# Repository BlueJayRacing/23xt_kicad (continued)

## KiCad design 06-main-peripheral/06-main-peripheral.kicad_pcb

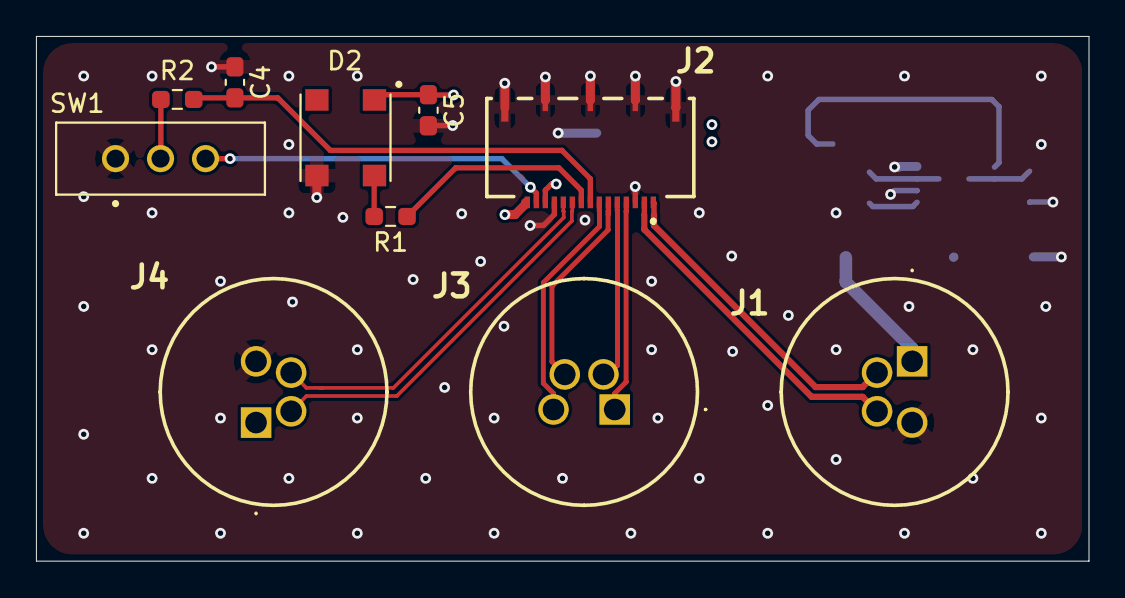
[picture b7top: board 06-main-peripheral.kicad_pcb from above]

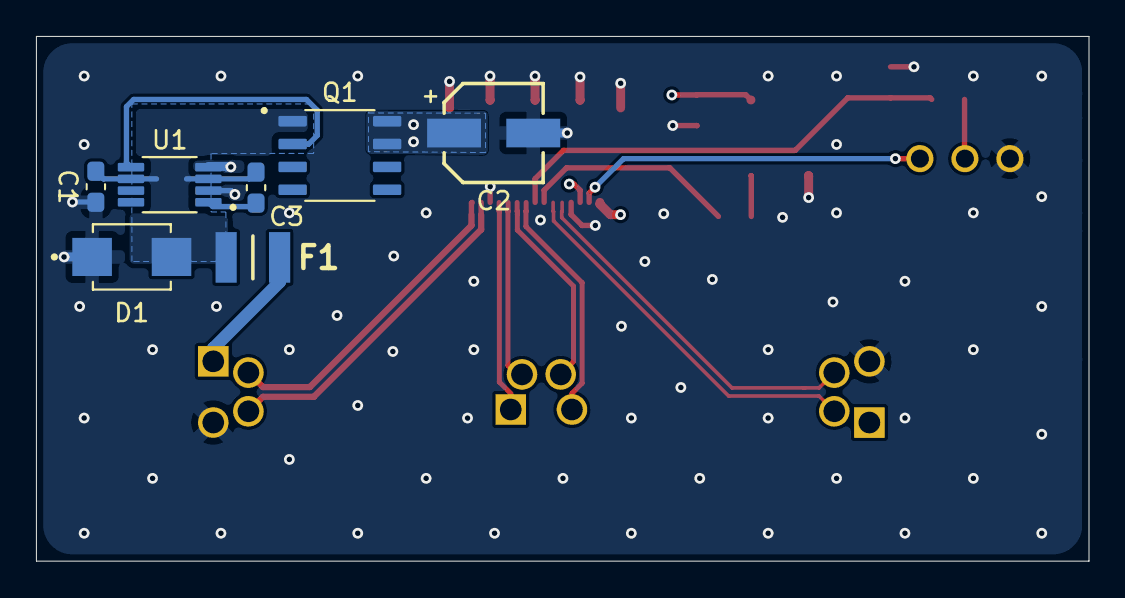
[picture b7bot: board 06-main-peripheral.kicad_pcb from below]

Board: 4 copper layers, 58.5 x 29.2 mm, 17 parts (7 on the bottom side), 20 nets.

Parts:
C1: 22nF; C_0603_1608Metric_Pad1.08x0.95mm_HandSolder
C2: 47uF; WCAP-ASLI_5X5.5_DXL_
C3: 0.1uF; C_0603_1608Metric_Pad1.08x0.95mm_HandSolder
C4, C5: 100nF; C_0603_1608Metric_Pad1.08x0.95mm_HandSolder
D1: SMBJ6.0CA; DIOM4336X265N
D2: LED 5050
F1: 0ZCH0050FF2G
J1, J3, J4: T4040014041000
J2: FH-41-15S-0.5SH-05_; FH4115S05SH05
Q1: DMN3018SSD-13; SOIC127P600X170-8N
R1: 500; R_0603_1608Metric_Pad0.98x0.95mm_HandSolder
R2: 10k; R_0603_1608Metric_Pad0.98x0.95mm_HandSolder
SW1: 100SP1K1B25M1QEH-ND; SW_EG1218
U1: LM74700-Q1; LM74610QDGKRQ1

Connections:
3.3V: J2.14, SW1.3 (A)
5V: C5.1, D2.3 (VDD), J2.15, J4.1
CAN_N: J2.11, J4.4
CAN_P: J2.10, J4.2
GND: C1.2, C2.2, C4.1, C5.2, D1.1 (A1), D2.1 (GND), J1.3, J2.3, J2.12, J2.G1, J2.G2, J2.G3, J2.MP2, J4.3, SW1.1 (C), U1.2 (GND), U1.4 (CATHODE)
LED_CONTROL: J2.9, R1.1
unnamed: C1.1, C3.1, D1.2 (A2), F1.1, Q1.1 (S), U1.3 (EN), U1.6 (ANODE)
unnamed: D2.2 (DIN), R1.2
unnamed: F1.2, J1.1
unnamed: Q1.2 (G), U1.5 (GATE)
unnamed: R2.2, SW1.2 (B)
unnamed: C3.2, U1.1 (VCAP)
RX_N: J2.5, J3.2
RX_P: J2.4, J3.1
TX_N: J2.6, J3.4
TX_P: J2.7, J3.3
USB_5V: C2.1, J2.13, Q1.7 (D), Q1.8
USB_D_N: J1.2, J2.1
USB_D_P: J1.4, J2.2
USB_SEL: C4.2, J2.8, R2.1

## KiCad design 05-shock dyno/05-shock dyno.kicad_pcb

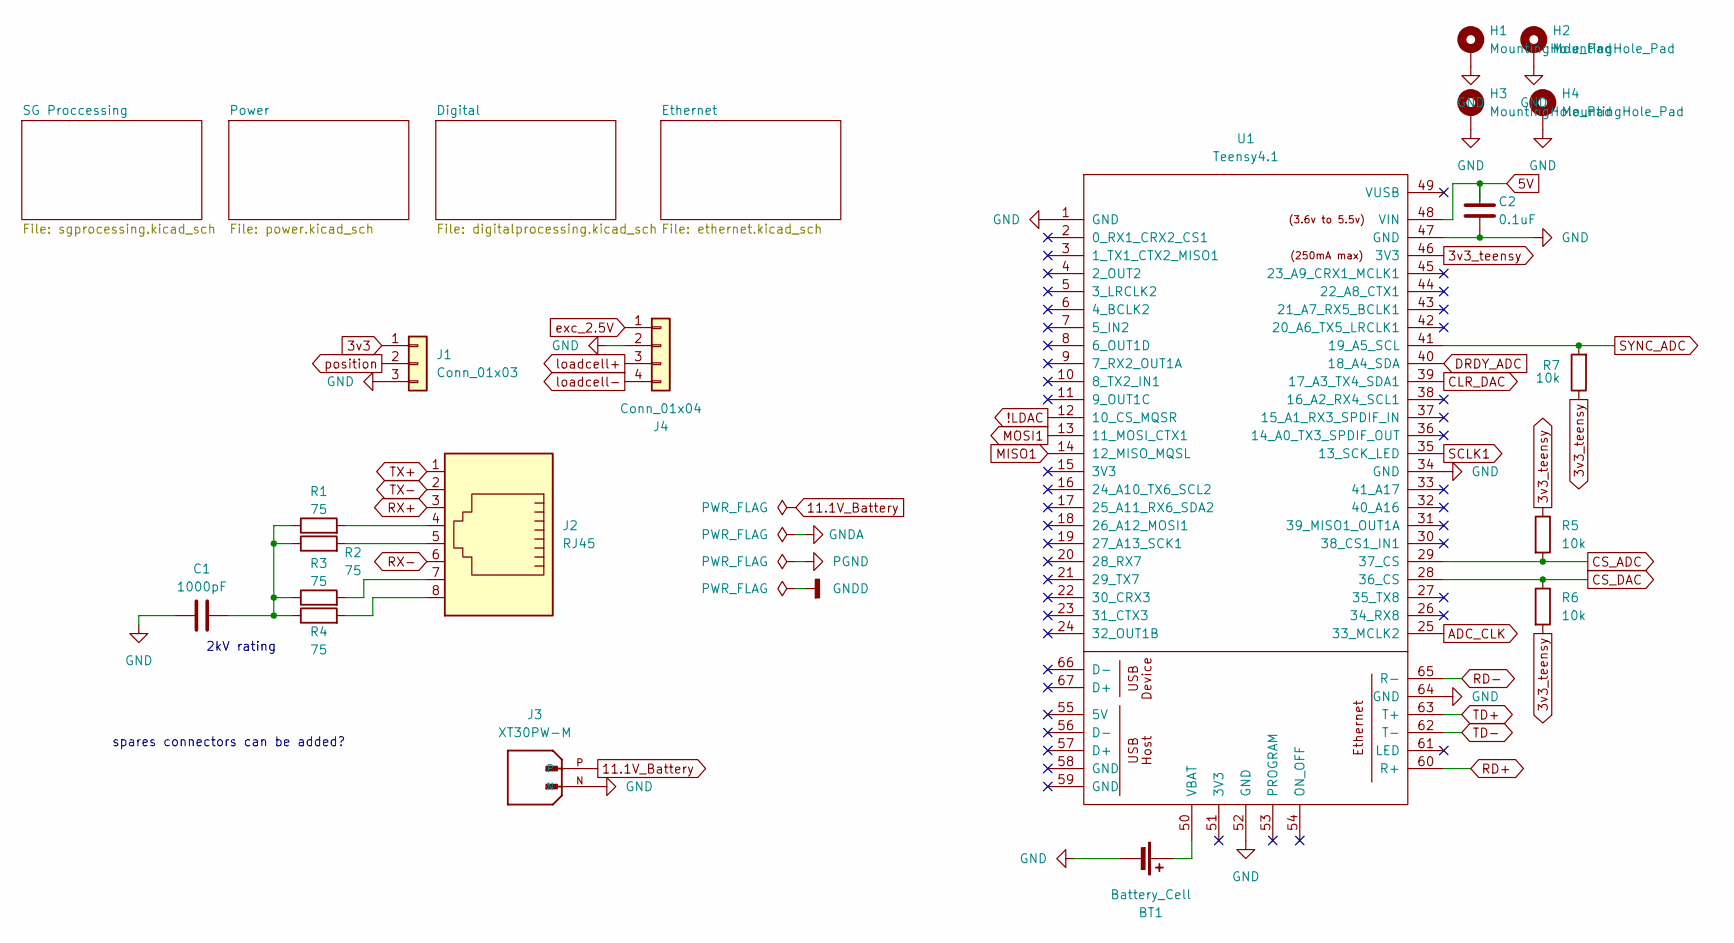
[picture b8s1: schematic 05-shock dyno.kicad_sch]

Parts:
BT1: Battery_Cell; BatteryHolder_LINX_BAT-HLD-012-SMT
C1: 1000pF; C_1206_3216Metric
C2: 0.1uF; C_0402_1005Metric
H1, H2, H3, H4: MountingHole_Pad; MountingHole_4.3mm_M4_DIN965_Pad
J1: Conn_01x03; JST_XH_B3B-XH-A_1x03_P2.50mm_Vertical
J2: RJ45; TE_RJ45-8N-B
J3: XT30PW-M; AMASS_XT30PW-M; PARTREV 1.2
J4: Conn_01x04; JST_XH_B4B-XH-A_1x04_P2.50mm_Vertical
R1, R2, R3, R4: 75; C_0402_1005Metric
R5, R6, R7: 10k; C_0402_1005Metric
U1: Teensy4.1; Teensy41

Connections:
3v3: J1.1; also elsewhere on the board
3v3_teensy: R5.1, R6.2, R7.1, U1.46 (3V3); also elsewhere on the board
5V: C2.1, U1.48 (VIN); also elsewhere on the board
11.1V_Battery: J3.P; also elsewhere on the board
!LDAC: U1.12 (10_CS_MQSR); also elsewhere on the board
ADC_CLK: U1.25 (33_MCLK2); also elsewhere on the board
CLR_DAC: U1.39 (17_A3_TX4_SDA1); also elsewhere on the board
CS_ADC: R5.2, U1.29 (37_CS); also elsewhere on the board
CS_DAC: R6.1, U1.28 (36_CS); also elsewhere on the board
DRDY_ADC: U1.40 (18_A4_SDA); also elsewhere on the board
GND: BT1.2 (-), C1.1, C2.2, H1.1, H2.1, H3.1, H4.1, J1.3, J3.N, J4.2, U1.1 (GND), U1.34 (GND), U1.47 (GND), U1.52 (GND), U1.64 (GND); also elsewhere on the board
MISO1: U1.14 (12_MISO_MQSL); also elsewhere on the board
MOSI1: U1.13 (11_MOSI_CTX1); also elsewhere on the board
unnamed: BT1.1 (+), U1.50 (VBAT)
unnamed: C1.2, R1.1, R2.1, R3.1, R4.1
unnamed: J2.4, R1.2
unnamed: J2.5, R2.2
unnamed: J2.7, R3.2
unnamed: J2.8, R4.2
RD+: U1.60 (R+); also elsewhere on the board
RD-: U1.65 (R-); also elsewhere on the board
RX+: J2.3; also elsewhere on the board
RX-: J2.6; also elsewhere on the board
SCLK1: U1.35 (13_SCK_LED); also elsewhere on the board
SYNC_ADC: R7.2, U1.41 (19_A5_SCL); also elsewhere on the board
TD+: U1.63 (T+); also elsewhere on the board
TD-: U1.62 (T-); also elsewhere on the board
TX+: J2.1; also elsewhere on the board
TX-: J2.2; also elsewhere on the board
exc_2.5V: J4.1; also elsewhere on the board
loadcell+: J4.3; also elsewhere on the board
loadcell-: J4.4; also elsewhere on the board
position: J1.2; also elsewhere on the board

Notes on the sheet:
2kV rating
spares connectors can be added?

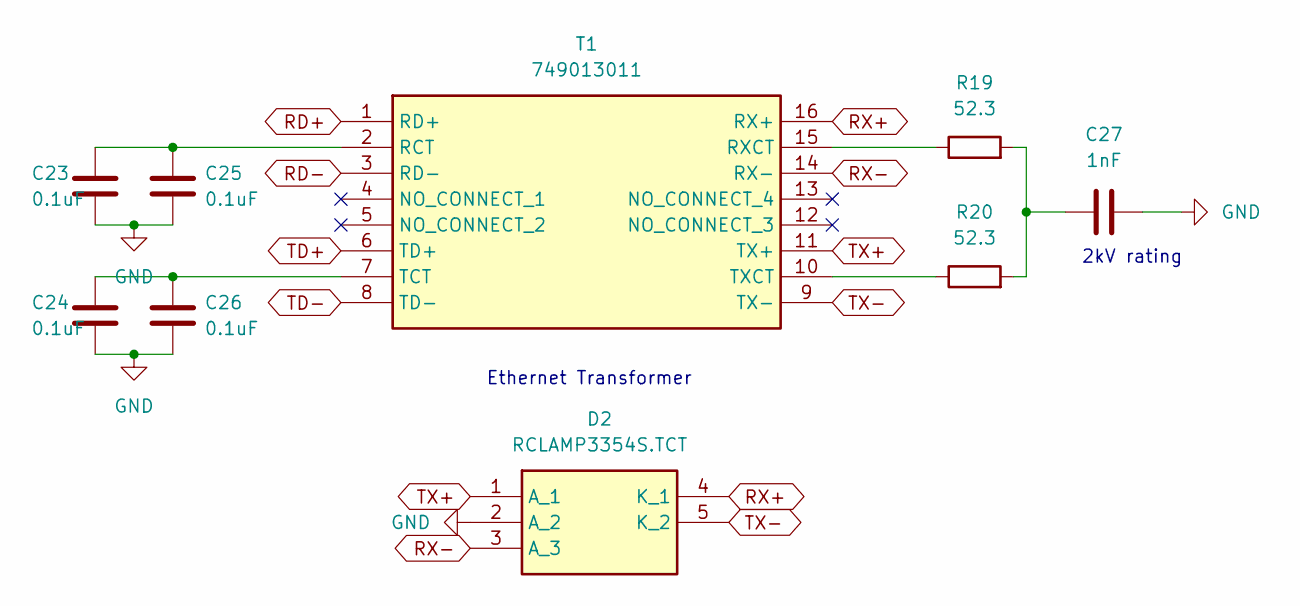
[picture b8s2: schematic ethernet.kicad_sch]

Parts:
C23, C24, C25, C26: 0.1uF; C_0402_1005Metric
C27: 1nF; C_1206_3216Metric
D2: RCLAMP3354S.TCT; SOT-23-5; Mouser Part Number 947-RCLAMP3354S.TCT
R19, R20: 52.3; C_0402_1005Metric
T1: 749013011; Mouser Part Number 710-749013011

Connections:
GND: C23.2, C24.2, C25.2, C26.2, C27.1, D2.2 (A_2); also elsewhere on the board
unnamed: C27.2, R19.2, R20.2
unnamed: C23.1, C25.1, T1.2 (RCT)
unnamed: R19.1, T1.15 (RXCT)
unnamed: C24.1, C26.1, T1.7 (TCT)
unnamed: R20.1, T1.10 (TXCT)
RD+: T1.1 (RD+); also elsewhere on the board
RD-: T1.3 (RD-); also elsewhere on the board
RX+: D2.4 (K_1), T1.16 (RX+); also elsewhere on the board
RX-: D2.3 (A_3), T1.14 (RX-); also elsewhere on the board
TD+: T1.6 (TD+); also elsewhere on the board
TD-: T1.8 (TD-); also elsewhere on the board
TX+: D2.1 (A_1), T1.11 (TX+); also elsewhere on the board
TX-: D2.5 (K_2), T1.9 (TX-); also elsewhere on the board

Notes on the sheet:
2kV rating
Ethernet Transformer

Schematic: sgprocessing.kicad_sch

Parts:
C3, C5: 1uF; C_0603_1608Metric
C4: 220nF; C_0603_1608Metric
C6, C8, C9, C11: 0.01uF; C_0603_1608Metric
C7, C10: 0.1uF; C_1206_3216Metric
IC1: ADS131M04IPWR; SOP65P640X120-20N; Mouser Part Number 595-ADS131M04IPWR
IC2: OPA320AIDBVR; SOT95P280X145-5N; Mouser Part Number 595-OPA320AIDBVR
R8: 20k; C_0603_1608Metric
R9: 10k; C_0603_1608Metric
R10, R11, R12, R13: 500; C_0603_1608Metric

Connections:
3v3: C3.1, IC1.1 (AVDD), IC2.5 (V+); also elsewhere on the board
3v3_teensy: C5.1, IC1.20 (DVDD); also elsewhere on the board
ADC_CLK: IC1.17 (CLKIN); also elsewhere on the board
CS_ADC: IC1.12 (~CS); also elsewhere on the board
DRDY_ADC: IC1.13 (~DRDY); also elsewhere on the board
GND: C3.2, C4.1, C5.2, C6.1, C8.2, C9.1, C11.2, IC1.2 (AGND), IC1.19 (DGND), IC2.2 (V-), R9.1, R13.1; also elsewhere on the board
MISO1: IC1.15 (DOUT); also elsewhere on the board
MOSI1: IC1.16 (DIN); also elsewhere on the board
unnamed: C4.2, IC1.18 (CAP)
unnamed: R8.2, R9.2, R12.1
SCLK1: IC1.14 (SCLK); also elsewhere on the board
SYNC_ADC: IC1.11 (~SYNC/~RESET); also elsewhere on the board
amp_ref_nyq+: C6.2, C7.1, IC1.3 (AIN0P), R10.2
amp_ref_nyq-: C7.2, C8.1, IC1.4 (AIN0N), R11.2
force_+: R10.1; also elsewhere on the board
force_-: R11.1; also elsewhere on the board
position: IC2.3 (+IN), IC2.4 (-IN); also elsewhere on the board
position_a: IC2.1 (OUT), R8.1
position_nyq+: C9.2, C10.1, IC1.6 (AIN1P), R12.2
position_nyq-: C10.2, C11.1, IC1.5 (AIN1N), R13.2

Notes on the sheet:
Buffer
ADC

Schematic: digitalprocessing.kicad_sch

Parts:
C19: 0.1uF; C_0402_1005Metric
C20, C22: 100pF; C_0603_1608Metric
C21: 1nF; C_0603_1608Metric
R16, R17: 1k; C_0603_1608Metric
R18: 511; C_0805_2012Metric
U3: AD5626BRMZ; MPN AD5626BRMZ
U4: INA827AIDGK

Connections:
5V: C19.1, U3.1 (VDD), U4.8 (+VS); also elsewhere on the board
!LDAC: U3.5 (LDAC*); also elsewhere on the board
CLR_DAC: U3.6 (CLR*); also elsewhere on the board
CS_DAC: U3.2 (CS*); also elsewhere on the board
GND: C19.2, C20.1, C22.1, U3.7 (GND), U4.5 (-VS); also elsewhere on the board
MOSI1: U3.4 (SDIN); also elsewhere on the board
unnamed: R18.1, U4.2 (RG2)
unnamed: R18.2, U4.3 (RG3)
SCLK1: U3.3 (SCLK); also elsewhere on the board
force_+: U4.7 (VOUT); also elsewhere on the board
force_-: U3.8 (VOUT), U4.6 (REF); also elsewhere on the board
loadcell+: R16.1; also elsewhere on the board
loadcell-: R17.1; also elsewhere on the board
loadcell_f+: C20.2, C21.1, R16.2, U4.4 (+IN)
loadcell_f-: C21.2, C22.2, R17.2, U4.1 (-IN)

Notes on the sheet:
DAC
set to 1.3V instead of 1.2V
ref pin need low impedance

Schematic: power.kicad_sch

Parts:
C12: 2.2uF; C_0805_2012Metric
C13: 10nF; C_0603_1608Metric
C14: 10uF; C_1206_3216Metric
C15: 22uF; C_1210_3225Metric
C16: 0.1uF; C_1206_3216Metric
C17: 1uF; C_0805_2012Metric
C18: 0.1uF; C_0603_1608Metric
D1: B340B-13-F; DIOM5336X250N
IC3: SPX3819S-L_TR; SOIC127P600X175-8N; Mouser Part Number 701-SPX3819S-L/TR
PS1: TSR_1-2450; TSR-1-24120; Mouser Part Number 495-TSR-1-2450
R14: 36.5k; C_0603_1608Metric
R15: 22.2k; C_0603_1608Metric
U2: REF5025ID; REF5025

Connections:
3v3: C12.1, C13.2, IC3.3 (VOUT), R14.1; also elsewhere on the board
5V: C15.1, C17.1, C18.1, IC3.1 (EN), IC3.2 (VIN), PS1.3 (VOUT+), U2.2 (VIN); also elsewhere on the board
11.1V: C14.2, C16.2, D1.1 (K), PS1.1 (VIN+)
11.1V_Battery: D1.2 (A); also elsewhere on the board
GND: C12.2, C14.1, C15.2, C16.1, C17.2, C18.2, IC3.5 (GND_1), IC3.6 (GND_2), IC3.7 (GND_3), IC3.8 (GND_4), PS1.2 (GND), R15.2, U2.4 (GND); also elsewhere on the board
unnamed: C13.1, IC3.4 (ADJ), R14.2, R15.1
exc_2.5V: U2.6 (VOUT); also elsewhere on the board

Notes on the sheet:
Vout: 3.30V

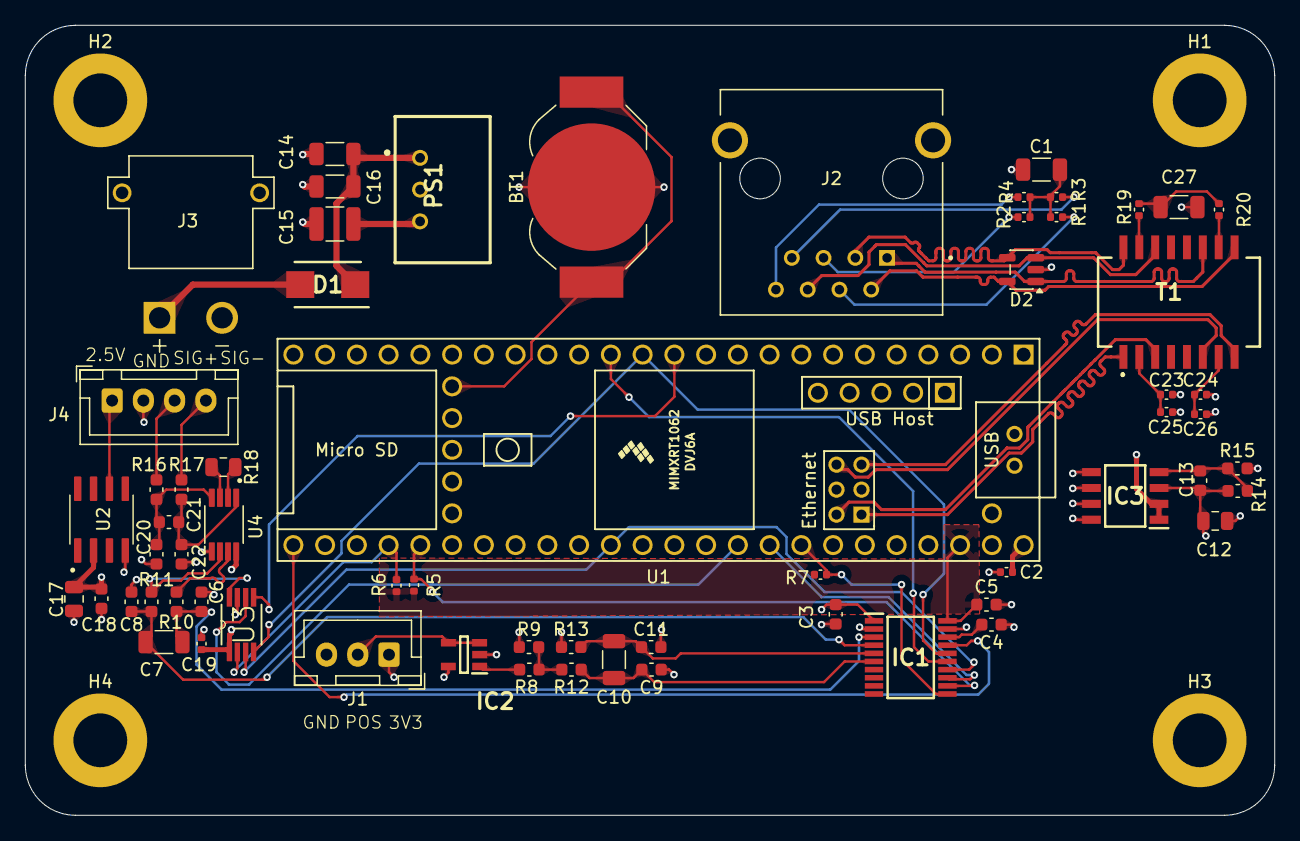
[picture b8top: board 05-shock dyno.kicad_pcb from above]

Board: 4 copper layers, 100.0 x 63.2 mm, 67 parts (0 on the bottom side), 53 nets.

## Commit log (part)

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2026-06-15 created project
2026-06-22 first try at kicad
2026-06-22 initial stm32 and ldo schematic
2026-06-22 add gitignore to exclude ds_store
2026-06-22 add magnetometer and can transceiver schematic
2026-06-25 schematic work
2026-06-25 add usbc flash and boot/reset
2026-06-30 transducer and hall preliminary design
